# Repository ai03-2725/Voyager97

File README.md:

# Voyager97
A versatile, modern full-functionality keyboard PCB

[PCB Layout](http://www.keyboard-layout-editor.com/#/gists/8a6f76a9ac2c94977268a77ed8a0af57)

#### In light of recent claims that I am 100% liable for any of my open source PCBs, I am adding this disclaimer.
#### I provide these PCBs as a reference for designing keyboard PCBs. Using them within your projects will require a will to do research of one's own and to learn the workings of them, potentially fixing issues if they exist.
# I provide these PCBs without liability and without any guarantees regarding functionality, as expressed in the MIT license under which all of these PCBs are licensed.

### Features
* In-switch LED backlighting
* RGB underglow
* Flex slot cutout for typing comfort
* Decent amount of layout compatibility
* Over-current and static discharge protection
* Fully open-source

### The Voyager PCB Family
The Voyager PCBs offer fully featured PCBs fit for any keyboard, whether mass production or high-end.

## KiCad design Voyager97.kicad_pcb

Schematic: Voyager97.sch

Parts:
C2, C5: 1uF; C_0603
C3, C4: 22pF; C_0603
C6, C7, C8: 0.1uF; C_0603
F1: 500mA; Fuse_SMD1206_Reflow
J1: AVR-ISP-6; Reset_Pretty-Mask
Q1: DSS60601MZ4-13; SOT-223-3_TabPin2
RC1, RC2: 22; R_0603
RC3: 10k; R_0603
RC4: 1k; R_0603
RC5: 1.5k; R_0603
RC6, RC7: 5k1; R_0603
SW1: SW_Push; SKQG-1155865
U1: AT90USB1286-AU; QFN-64-1EP_9x9mm_Pitch0.5mm
U2: PRTR5V0U2X; SOT143B
USB1: HRO-TYPE-C-31-M-12; HRO-TYPE-C-31-M-12-Assembly
Y1: 16MHz; Crystal_SMD_3225-4pin_3.2x2.5mm

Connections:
COL0: U1.61 (PF0); also elsewhere on the board
COL1: U1.60 (PF1); also elsewhere on the board
COL2: U1.59 (PF2); also elsewhere on the board
COL3: U1.58 (PF3); also elsewhere on the board
COL4: U1.57 (PF4); also elsewhere on the board
COL5: U1.56 (PF5); also elsewhere on the board
COL6: U1.55 (PF6); also elsewhere on the board
COL7: U1.54 (PF7); also elsewhere on the board
COL8: U1.51 (PA0); also elsewhere on the board
COL9: U1.50 (PA1); also elsewhere on the board
COL10: U1.49 (PA2); also elsewhere on the board
COL11: U1.48 (PA3); also elsewhere on the board
COL12: U1.47 (PA4); also elsewhere on the board
COL13: U1.46 (PA5); also elsewhere on the board
COL14: U1.45 (PA6); also elsewhere on the board
COL15: U1.36 (PC1); also elsewhere on the board
COL16: U1.35 (PC0); also elsewhere on the board
COL17: U1.34 (PE1); also elsewhere on the board
COL18: U1.33 (PE0); also elsewhere on the board
D+: RC2.2, U1.5 (D+)
D-: RC1.1, U1.4 (D-)
GND: C2.2, C3.2, C4.2, C5.1, C6.1, C7.1, C8.1, J1.6, Q1.3, RC4.2, RC6.1, RC7.1, SW1.1, U1.6 (UGND), U1.22 (GND), U1.53 (GND), U1.63 (GND), U1.65 (GND), U2.1, USB1.1, USB1.12, USB1.13, Y1.2, Y1.4
LEDGND: Q1.2; also elsewhere on the board
MISO: J1.1, U1.13 (PB3)
MOSI: J1.4, U1.12 (PB2)
unnamed: C2.1, U1.7 (UCAP)
unnamed: Q1.1, RC5.2
unnamed: RC1.2, U2.3, USB1.5, USB1.7
unnamed: RC2.1, U2.2, USB1.6, USB1.8
unnamed: RC4.1, U1.43 (PE2/~HWB)
unnamed: RC5.1, U1.17 (PB7)
unnamed: RC6.2, USB1.4
unnamed: RC7.2, USB1.10
RESET: J1.5, RC3.2, SW1.2, U1.20 (~RESET)
ROW0: U1.32 (PD7); also elsewhere on the board
ROW1: U1.38 (PC3); also elsewhere on the board
ROW2: U1.39 (PC4); also elsewhere on the board
ROW3: U1.40 (PC5); also elsewhere on the board
ROW4: U1.41 (PC6); also elsewhere on the board
ROW5: U1.42 (PC7); also elsewhere on the board
SCK: J1.3, U1.11 (PB1)
VCC: F1.2, U2.4, USB1.2, USB1.11
XTAL1: C3.1, U1.24 (XTAL1), Y1.1
XTAL2: C4.1, U1.23 (XTAL2), Y1.3

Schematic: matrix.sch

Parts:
BS1-1: MX-2U
BS1-2, BS2: MX-1U
CL1-1: MX-1.75U
CL1-2: MX-1.25U; MX-1.25U-FLIPPED
D1, D2, D3, D4, D5, D6, D7, D8, D9, D10, D11, D12, D13, D14, D15, D16, D17, D18, D19, D20, D21, D22, D23, D24, D25, D26, D27, D28, D29, D30, D31, D32, D33, D35, D36, D37, D38, D39, D40, D41, D42, D43, D44, D45, D46, D47, D48, D52, D53, D54, D55, D56, D57, D58, D59, D60, D61, D62, D63, D65, D66, D67, D68, D69, D70, D71, D72, D73, D74, D75, D76, D77, D78, D80, D81, D82, D83, D84, D85, D86, D87, D89, D90, D91, D92, D93, D94, D95, D96, D97, D98, D99, D100, D101, D102, D103, D104, D105, D106, D107, D108, D109, D110, D111, D112, D113, D114: SOD-323; D_SOD-123
LM1-1, LM2-1, LM3-1: MX-1.25U
LM1-2: MX-1.5U; MX-1.5U-FLIPPED
LM3-2: MX-1.5U
LS1-1: MX-2.25U
MX_#0_1, MX_#1, MX_#2, MX_#3, MX_#4, MX_#5, MX_#6, MX_#7, MX_#8, MX_#9: MX-1U
MX_'1: MX-1U
MX_,1: MX-1U
MX_-1: MX-1U
MX_.1: MX-1U
MX_/1: MX-1U
MX_;1: MX-1U
MX_=1: MX-1U
MX_A1: MX-1U
MX_B1: MX-1U
MX_C1: MX-1U
MX_D1: MX-1U
MX_DOWN1: MX-1U
MX_E1: MX-1U
MX_ESC1: MX-1U
MX_EX1, MX_EX2, MX_EX3, MX_EX4: MX-1U
MX_F1: MX-1U
MX_FN1, MX_FN2, MX_FN3, MX_FN4, MX_FN5, MX_FN6, MX_FN7, MX_FN8, MX_FN9, MX_FN10, MX_FN11, MX_FN12: MX-1U
MX_G1: MX-1U
MX_H1: MX-1U
MX_I1: MX-1U
MX_J1: MX-1U
MX_K1: MX-1U
MX_L1: MX-1U
MX_LEFT1: MX-1U
MX_M1: MX-1U
MX_N1: MX-1U
MX_NUM1, MX_NUM2, MX_NUM3, MX_NUM4, MX_NUM5, MX_NUM6, MX_NUM7, MX_NUM8, MX_NUM9, MX_NUM10, MX_NUM11, MX_NUM12, MX_NUM13, MX_NUM14, MX_NUM15, MX_NUM16, MX_NUM17, MX_NUM18, MX_NUM19, MX_NUM20, MX_NUM21, MX_NUM22, MX_NUM23, MX_NUM24: MX-1U
MX_NUMEXT2, MX_NUMEXT4, MX_NUMEXT5: MX-2U; MX-2U-ReversedStabilizers
MX_O1: MX-1U
MX_P1: MX-1U
MX_Q1: MX-1U
MX_R1: MX-1U
MX_RESET1: MX-1U
MX_RETURN1: MX-2.25U
MX_RIGHT1: MX-1U
MX_RSHIFT1: MX-1.75U
MX_S1: MX-1U
MX_T1: MX-1U
MX_TAB1: MX-1.5U
MX_U1: MX-1U
MX_UP1: MX-1U
MX_V1: MX-1U
MX_W1: MX-1U
MX_X1: MX-1U
MX_Y1: MX-1U
MX_Z1: MX-1U
MX_[1: MX-1U
MX_\1: MX-1.5U
MX_]1: MX-1U
MX_`1: MX-1U
R1, R2, R3, R4, R5, R6, R7, R8, R9, R10, R11, R12, R13, R14, R15, R16, R17, R18, R19, R20, R21, R22, R23, R24, R25, R26, R27, R28, R29, R30, R31, R32, R33, R34, R35, R36, R37, R38, R39, R40, R41, R42, R43, R44, R45, R46, R47, R48, R49, R50, R52, R53, R54, R55, R56, R57, R58, R59, R60, R61, R62, R63, R65, R66, R67, R68, R69, R70, R71, R72, R73, R74, R75, R76, R77, R78, R80, R81, R82, R83, R84, R85, R86, R87, R89, R90, R91, R95, R96, R97, R98, R99, R100, R101, R102, R103, R104, R105, R106, R107, R108, R109, R110, R111, R112, R113, R114: 1k; R_0603
RM1-1, RM2-1, RM3-1: MX-1U
RM1-2, RM3-2: MX-1.5U; MX-1.5U-FLIPPED
SP1: MX-6.25U; MX-6.25U-ReversedStabilizers
SP2: MX-7U; MX-7U-ReversedStabilizers

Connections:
COL0: CL1-1.1, CL1-2.2, LM1-1.1, LM1-2.1, LS1-1.1, MX_ESC1.1, MX_TAB1.1, MX_`1.1; also elsewhere on the board
COL1: LM2-1.1, LM3-2.2, MX_#1.1, MX_A1.1, MX_Q1.1, MX_Z1.1; also elsewhere on the board
COL2: LM3-1.1, MX_#2.1, MX_FN1.1, MX_S1.1, MX_W1.1, MX_X1.1; also elsewhere on the board
COL3: MX_#3.1, MX_C1.1, MX_D1.1, MX_E1.1, MX_FN2.1; also elsewhere on the board
COL4: MX_#4.1, MX_F1.1, MX_FN3.1, MX_R1.1, MX_V1.1; also elsewhere on the board
COL5: MX_#5.1, MX_B1.1, MX_FN4.1, MX_G1.1, MX_T1.1, SP1.1, SP2.2; also elsewhere on the board
COL6: MX_#6.1, MX_FN5.1, MX_H1.1, MX_N1.1, MX_Y1.1; also elsewhere on the board
COL7: MX_#7.1, MX_FN6.1, MX_J1.1, MX_M1.1, MX_U1.1; also elsewhere on the board
COL8: MX_#8.1, MX_,1.1, MX_FN7.1, MX_I1.1, MX_K1.1; also elsewhere on the board
COL9: MX_#9.1, MX_.1.1, MX_FN8.1, MX_L1.1, MX_O1.1, RM1-1.1, RM1-2.2; also elsewhere on the board
COL10: MX_#0_1.1, MX_/1.1, MX_;1.1, MX_FN9.1, MX_P1.1, RM2-1.1; also elsewhere on the board
COL11: MX_'1.1, MX_-1.1, MX_FN10.1, MX_[1.1, RM3-1.1, RM3-2.2; also elsewhere on the board
COL12: BS2.1, MX_=1.1, MX_FN11.1, MX_LEFT1.1, MX_RSHIFT1.1, MX_]1.1; also elsewhere on the board
COL13: BS1-1.1, BS1-2.1, MX_DOWN1.1, MX_FN12.1, MX_RETURN1.1, MX_UP1.1, MX_\1.1; also elsewhere on the board
COL14: MX_EX1.1, MX_EX2.1, MX_EX3.1, MX_EX4.1, MX_RESET1.1, MX_RIGHT1.1; also elsewhere on the board
COL15: MX_NUM1.1, MX_NUM4.1, MX_NUM8.1, MX_NUM12.1, MX_NUM16.1, MX_NUM20.1, MX_NUMEXT5.1; also elsewhere on the board
COL16: MX_NUM2.1, MX_NUM5.1, MX_NUM9.1, MX_NUM13.1, MX_NUM17.1, MX_NUM21.1; also elsewhere on the board
COL17: MX_NUM3.1, MX_NUM6.1, MX_NUM10.1, MX_NUM14.1, MX_NUM18.1, MX_NUM22.1; also elsewhere on the board
COL18: MX_NUM7.1, MX_NUM11.1, MX_NUM15.1, MX_NUM19.1, MX_NUM23.1, MX_NUM24.1, MX_NUMEXT2.1, MX_NUMEXT4.1; also elsewhere on the board
LEDGND: R1.2, R2.2, R3.2, R4.2, R5.2, R6.2, R7.2, R8.2, R9.2, R10.2, R11.2, R12.2, R13.2, R14.2, R15.2, R16.2, R17.2, R18.2, R19.2, R20.2, R21.2, R22.2, R23.2, R24.2, R25.2, R26.2, R27.2, R28.2, R29.2, R30.2, R31.2, R32.2, R33.2, R34.2, R35.2, R36.2, R37.2, R38.2, R39.2, R40.2, R41.2, R42.2, R43.2, R44.2, R45.2, R46.2, R47.2, R48.2, R49.2, R50.2, R52.2, R53.2, R54.2, R55.2, R56.2, R57.2, R58.2, R59.2, R60.2, R61.2, R62.2, R63.2, R65.2, R66.2, R67.2, R68.2, R69.2, R70.2, R71.2, R72.2, R73.2, R74.2, R75.2, R76.2, R77.2, R78.2, R80.2, R81.2, R82.2, R83.2, R84.2, R85.2, R86.2, R87.2, R89.2, R90.2, R91.2, R95.2, R96.2, R97.2, R98.2, R99.2, R100.2, R101.2, R102.2, R103.2, R104.2, R105.2, R106.2, R107.2, R108.2, R109.2, R110.2, R111.2, R112.2, R113.2, R114.2; also elsewhere on the board
unnamed: BS1-1.2, BS1-2.2, D30.2
unnamed: BS1-1.4, BS1-2.4, R30.1
unnamed: BS2.2, D31.2
unnamed: BS2.4, R31.1
unnamed: CL1-1.2, CL1-2.1, D52.2
unnamed: CL1-1.4, CL1-2.4, R52.1
unnamed: D1.2, MX_ESC1.2
unnamed: D2.2, MX_FN1.2
unnamed: D3.2, MX_FN2.2
unnamed: D4.2, MX_FN3.2
unnamed: D5.2, MX_FN4.2
unnamed: D6.2, MX_FN5.2
unnamed: D7.2, MX_FN6.2
unnamed: D8.2, MX_FN7.2
unnamed: D9.2, MX_FN8.2
unnamed: D10.2, MX_FN9.2
unnamed: D11.2, MX_FN10.2
unnamed: D12.2, MX_FN11.2
unnamed: D13.2, MX_FN12.2
unnamed: D14.2, MX_EX1.2
unnamed: D15.2, MX_RESET1.2
unnamed: D16.2, MX_NUM24.2
unnamed: D17.2, MX_`1.2
unnamed: D18.2, MX_#1.2
unnamed: D19.2, MX_#2.2
unnamed: D20.2, MX_#3.2
unnamed: D21.2, MX_#4.2
unnamed: D22.2, MX_#5.2
unnamed: D23.2, MX_#6.2
unnamed: D24.2, MX_#7.2
unnamed: D25.2, MX_#8.2
unnamed: D26.2, MX_#9.2
unnamed: D27.2, MX_#0_1.2
unnamed: D28.2, MX_-1.2
unnamed: D29.2, MX_=1.2
unnamed: D32.2, MX_EX2.2
unnamed: D33.2, MX_EX3.2
unnamed: D35.2, MX_TAB1.2
unnamed: D36.2, MX_Q1.2
unnamed: D37.2, MX_W1.2
unnamed: D38.2, MX_E1.2
unnamed: D39.2, MX_R1.2
unnamed: D40.2, MX_T1.2
unnamed: D41.2, MX_Y1.2
unnamed: D42.2, MX_U1.2
unnamed: D43.2, MX_I1.2
unnamed: D44.2, MX_O1.2
unnamed: D45.2, MX_P1.2
unnamed: D46.2, MX_[1.2
unnamed: D47.2, MX_]1.2
unnamed: D48.2, MX_\1.2
unnamed: D53.2, MX_A1.2
unnamed: D54.2, MX_S1.2
unnamed: D55.2, MX_D1.2
unnamed: D56.2, MX_F1.2
unnamed: D57.2, MX_G1.2
unnamed: D58.2, MX_H1.2
unnamed: D59.2, MX_J1.2
unnamed: D60.2, MX_K1.2
unnamed: D61.2, MX_L1.2
unnamed: D62.2, MX_;1.2
unnamed: D63.2, MX_'1.2
unnamed: D65.2, MX_RETURN1.2
unnamed: D66.2, MX_UP1.2
unnamed: D67.2, LS1-1.2
unnamed: D68.2, MX_Z1.2
unnamed: D69.2, MX_X1.2
unnamed: D70.2, MX_C1.2
unnamed: D71.2, MX_V1.2
unnamed: D72.2, MX_B1.2
unnamed: D73.2, MX_N1.2
unnamed: D74.2, MX_M1.2
unnamed: D75.2, MX_,1.2
unnamed: D76.2, MX_.1.2
unnamed: D77.2, MX_/1.2
unnamed: D78.2, MX_RSHIFT1.2
unnamed: D80.2, MX_EX4.2
unnamed: D81.2, MX_LEFT1.2
unnamed: D82.2, MX_DOWN1.2
unnamed: D83.2, MX_RIGHT1.2
unnamed: D84.2, LM1-1.2, LM1-2.2
unnamed: D85.2, LM2-1.2, LM3-2.1
unnamed: D86.2, LM3-1.2
unnamed: D87.2, SP1.2, SP2.1
unnamed: D89.2, RM1-1.2, RM1-2.1
unnamed: D90.2, RM2-1.2
unnamed: D91.2, RM3-1.2, RM3-2.1
unnamed: D92.2, MX_NUM1.2
unnamed: D93.2, MX_NUM2.2
unnamed: D94.2, MX_NUM3.2
unnamed: D95.2, MX_NUM4.2
unnamed: D96.2, MX_NUM5.2
unnamed: D97.2, MX_NUM6.2
unnamed: D98.2, MX_NUM7.2
unnamed: D99.2, MX_NUM8.2
unnamed: D100.2, MX_NUM9.2
unnamed: D101.2, MX_NUM10.2
unnamed: D102.2, MX_NUM11.2, MX_NUMEXT2.2
unnamed: D103.2, MX_NUM12.2
unnamed: D104.2, MX_NUM13.2
unnamed: D105.2, MX_NUM14.2
unnamed: D106.2, MX_NUM15.2
unnamed: D107.2, MX_NUM16.2
unnamed: D108.2, MX_NUM17.2
unnamed: D109.2, MX_NUM18.2
unnamed: D110.2, MX_NUM19.2, MX_NUMEXT4.2
unnamed: D111.2, MX_NUM20.2, MX_NUMEXT5.2
unnamed: D112.2, MX_NUM21.2
unnamed: D113.2, MX_NUM22.2
unnamed: D114.2, MX_NUM23.2
unnamed: LM1-1.4, LM1-2.4, R84.1
unnamed: LM2-1.4, LM3-2.4, R85.1
unnamed: LM3-1.4, R86.1
unnamed: LS1-1.4, R67.1
unnamed: MX_#0_1.4, R27.1
unnamed: MX_#1.4, R18.1
unnamed: MX_#2.4, R19.1
unnamed: MX_#3.4, R20.1
unnamed: MX_#4.4, R21.1
unnamed: MX_#5.4, R22.1
unnamed: MX_#6.4, R23.1
unnamed: MX_#7.4, R24.1
unnamed: MX_#8.4, R25.1
unnamed: MX_#9.4, R26.1
unnamed: MX_'1.4, R63.1
unnamed: MX_,1.4, R75.1
unnamed: MX_-1.4, R28.1
unnamed: MX_.1.4, R76.1
unnamed: MX_/1.4, R77.1
unnamed: MX_;1.4, R62.1
unnamed: MX_=1.4, R29.1
unnamed: MX_A1.4, R53.1
unnamed: MX_B1.4, R72.1
unnamed: MX_C1.4, R70.1
unnamed: MX_D1.4, R55.1
unnamed: MX_DOWN1.4, R82.1
unnamed: MX_E1.4, R38.1
unnamed: MX_ESC1.4, R1.1
unnamed: MX_EX1.4, R14.1
unnamed: MX_EX2.4, R49.1
unnamed: MX_EX3.4, R50.1
unnamed: MX_EX4.4, R80.1
unnamed: MX_F1.4, R56.1
unnamed: MX_FN1.4, R2.1
unnamed: MX_FN2.4, R3.1
unnamed: MX_FN3.4, R4.1
unnamed: MX_FN4.4, R5.1
unnamed: MX_FN5.4, R6.1
unnamed: MX_FN6.4, R7.1
unnamed: MX_FN7.4, R8.1
unnamed: MX_FN8.4, R9.1
unnamed: MX_FN9.4, R10.1
unnamed: MX_FN10.4, R11.1
unnamed: MX_FN11.4, R12.1
unnamed: MX_FN12.4, R13.1
unnamed: MX_G1.4, R57.1
unnamed: MX_H1.4, R58.1
unnamed: MX_I1.4, R43.1
unnamed: MX_J1.4, R59.1
unnamed: MX_K1.4, R60.1
unnamed: MX_L1.4, R61.1
unnamed: MX_LEFT1.4, R81.1
unnamed: MX_M1.4, R74.1
unnamed: MX_N1.4, R73.1
unnamed: MX_NUM1.4, R16.1
unnamed: MX_NUM2.4, R32.1
unnamed: MX_NUM3.4, R33.1
unnamed: MX_NUM4.4, R95.1
unnamed: MX_NUM5.4, R96.1
unnamed: MX_NUM6.4, R97.1
unnamed: MX_NUM7.4, R98.1
unnamed: MX_NUM8.4, R99.1
unnamed: MX_NUM9.4, R100.1
unnamed: MX_NUM10.4, R101.1
unnamed: MX_NUM11.4, MX_NUMEXT2.4, R102.1
unnamed: MX_NUM12.4, R103.1
unnamed: MX_NUM13.4, R104.1
unnamed: MX_NUM14.4, R105.1
unnamed: MX_NUM15.4, R106.1
unnamed: MX_NUM16.4, R107.1
unnamed: MX_NUM17.4, R108.1
unnamed: MX_NUM18.4, R109.1
unnamed: MX_NUM19.4, MX_NUMEXT4.4, R110.1
unnamed: MX_NUM20.4, MX_NUMEXT5.4, R111.1
unnamed: MX_NUM21.4, R112.1
unnamed: MX_NUM22.4, R113.1
unnamed: MX_NUM23.4, R114.1
unnamed: MX_NUM24.4, R34.1
unnamed: MX_O1.4, R44.1
unnamed: MX_P1.4, R45.1
unnamed: MX_Q1.4, R36.1
unnamed: MX_R1.4, R39.1
unnamed: MX_RESET1.4, R15.1
unnamed: MX_RETURN1.4, R65.1
unnamed: MX_RIGHT1.4, R83.1
unnamed: MX_RSHIFT1.4, R78.1
unnamed: MX_S1.4, R54.1
unnamed: MX_T1.4, R40.1
unnamed: MX_TAB1.4, R35.1
unnamed: MX_U1.4, R42.1
unnamed: MX_UP1.4, R66.1
unnamed: MX_V1.4, R71.1
unnamed: MX_W1.4, R37.1
unnamed: MX_X1.4, R69.1
unnamed: MX_Y1.4, R41.1
unnamed: MX_Z1.4, R68.1
unnamed: MX_[1.4, R46.1
unnamed: MX_\1.4, R48.1
unnamed: MX_]1.4, R47.1
unnamed: MX_`1.4, R17.1
unnamed: R87.1, SP1.4, SP2.4
unnamed: R89.1, RM1-1.4, RM1-2.4
unnamed: R90.1, RM2-1.4
unnamed: R91.1, RM3-1.4, RM3-2.4
ROW0: D1.1, D2.1, D3.1, D4.1, D5.1, D6.1, D7.1, D8.1, D9.1, D10.1, D11.1, D12.1, D13.1, D15.1, D16.1, D92.1, D93.1, D94.1; also elsewhere on the board
ROW1: D14.1, D17.1, D18.1, D19.1, D20.1, D21.1, D22.1, D23.1, D24.1, D25.1, D26.1, D27.1, D28.1, D29.1, D30.1, D95.1, D96.1, D97.1, D98.1; also elsewhere on the board
ROW2: D32.1, D35.1, D36.1, D37.1, D38.1, D39.1, D40.1, D41.1, D42.1, D43.1, D44.1, D45.1, D46.1, D47.1, D48.1, D99.1, D100.1, D101.1, D102.1; also elsewhere on the board
ROW3: D31.1, D33.1, D52.1, D53.1, D54.1, D55.1, D56.1, D57.1, D58.1, D59.1, D60.1, D61.1, D62.1, D63.1, D65.1, D103.1, D104.1, D105.1, D106.1; also elsewhere on the board
ROW4: D66.1, D67.1, D68.1, D69.1, D70.1, D71.1, D72.1, D73.1, D74.1, D75.1, D76.1, D77.1, D78.1, D80.1, D107.1, D108.1, D109.1, D110.1; also elsewhere on the board
ROW5: D81.1, D82.1, D83.1, D84.1, D85.1, D86.1, D87.1, D89.1, D90.1, D91.1, D111.1, D112.1, D113.1, D114.1; also elsewhere on the board

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
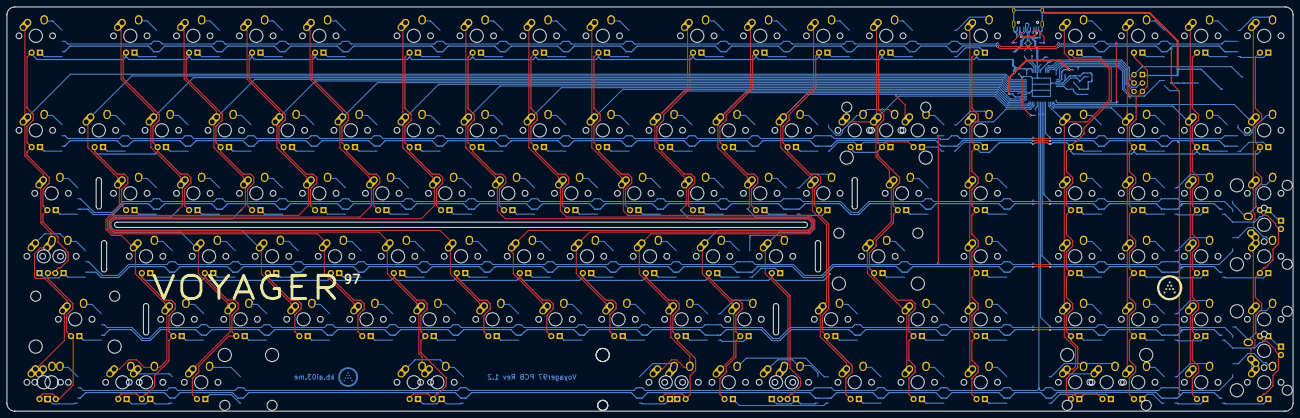
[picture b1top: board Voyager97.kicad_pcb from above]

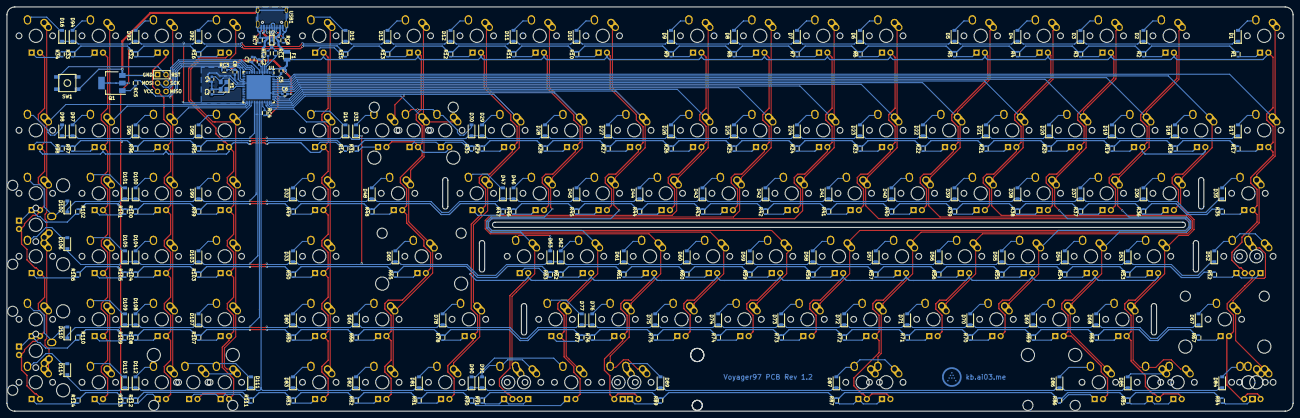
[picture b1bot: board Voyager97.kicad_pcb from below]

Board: 2 copper layers, 388.9 x 122.2 mm, 353 parts (236 on the bottom side), 259 nets.

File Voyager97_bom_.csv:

Component,Description,Part,References,Value,Footprint,Quantity Per PCB,Datasheet,Field8,Field4,Field7,Field6,Field5
1,,MX-1U,"BS1-2 BS2 MX_#0_1 MX_#1 MX_#2 MX_#3 MX_#4 MX_#5 MX_#6 MX_#7 MX_#8 MX_#9 MX_'1 MX_,1 MX_-1 MX_.1 MX_/1 MX_;1 MX_=1 MX_A1 MX_B1 MX_C1 MX_D1 MX_DOWN1 MX_E1 MX_ESC1 MX_EX1 MX_EX2 MX_EX3 MX_EX4 MX_F1 MX_FN1 MX_FN2 MX_FN3 MX_FN4 MX_FN5 MX_FN6 MX_FN7 MX_FN8 MX_FN9 MX_FN10 MX_FN11 MX_FN12 MX_G1 MX_H1 MX_I1 MX_J1 MX_K1 MX_L1 MX_LEFT1 MX_M1 MX_N1 MX_NUM1 MX_NUM2 MX_NUM3 MX_NUM4 MX_NUM5 MX_NUM6 MX_NUM7 MX_NUM8 MX_NUM9 MX_NUM10 MX_NUM11 MX_NUM12 MX_NUM13 MX_NUM14 MX_NUM15 MX_NUM16 MX_NUM17 MX_NUM18 MX_NUM19 MX_NUM20 MX_NUM21 MX_NUM22 MX_NUM23 MX_NUM24 MX_O1 MX_P1 MX_Q1 MX_R1 MX_RESET1 MX_RIGHT1 MX_S1 MX_T1 MX_U1 MX_UP1 MX_V1 MX_W1 MX_X1 MX_Y1 MX_Z1 MX_[1 MX_]1 MX_`1",MX-1U,MX-1U,94,,,,,,
2,,MX-2U,BS1-1,MX-2U,MX-2U,1,,,,,,
3,Unpolarized capacitor,C_Small,C6 C7 C8,0.1uF,C_0603,3,,,,,,
4,Unpolarized capacitor,C_Small,C2 C5,1uF,C_0603,2,,,,,,
5,Unpolarized capacitor,C_Small,C3 C4,22pF,C_0603,2,,,,,,
6,,MX-1.25U,CL1-2,MX-1.25U,MX-1.25U-FLIPPED,1,,,,,,
7,,MX-1.75U,CL1-1,MX-1.75U,MX-1.75U,1,,,,,,
8,"Diode, small symbol",D_Small,D1 D2 D3 D4 D5 D6 D7 D8 D9 D10 D11 D12 D13 D14 D15 D16 D17 D18 D19 D20 D21 D22 D23 D24 D25 D26 D27 D28 D29 D30 D31 D32 D33 D35 D36 D37 D38 D39 D40 D41 D42 D43 D44 D45 D46 D47 D48 D52 D53 D54 D55 D56 D57 D58 D59 D60 D61 D62 D63 D65 D66 D67 D68 D69 D70 D71 D72 D73 D74 D75 D76 D77 D78 D80 D81 D82 D83 D84 D85 D86 D87 D89 D90 D91 D92 D93 D94 D95 D96 D97 D98 D99 D100 D101 D102 D103 D104 D105 D106 D107 D108 D109 D110 D111 D112 D113 D114,SOD-323,D_SOD-123,107,,,,,,
9,"resettable fuse, polymeric positive temperature coefficient (PPTC), small symbol",Polyfuse_Small,F1,500mA,Fuse_SMD1206_Reflow,1,,,,,,
10,Atmel 6-pin ISP connector,AVR-ISP-6,J1,AVR-ISP-6,Reset_Pretty-Mask,1, ~,,,,,
11,,MX-1U,LM1-1,MX-1.25U,MX-1.25U,1,,,,,,
12,,MX-1.25U,LM2-1 LM3-1,MX-1.25U,MX-1.25U,2,,,,,,
13,,MX-1.5U,LM1-2 RM1-2 RM3-2,MX-1.5U,MX-1.5U-FLIPPED,3,,,,,,
14,,MX-1.5U,LM3-2 MX_TAB1 MX_\1,MX-1.5U,MX-1.5U,3,,,,,,
15,,MX-2.25U,LS1-1 MX_RETURN1,MX-2.25U,MX-2.25U,2,,,,,,
16,,MX-1U,MX_RSHIFT1,MX-1.75U,MX-1.75U,1,,,,,,
17,,MX-1U,MX_NUMEXT2 MX_NUMEXT4 MX_NUMEXT5,MX-2U,MX-2U-ReversedStabilizers,3,,,,,,
18,Transistor NPN (general),Q_NPN_BCE,Q1,DSS60601MZ4-13,SOT-223-3_TabPin2,1,,,,,,
19,"Resistor, small symbol",R_Small,R1 R2 R3 R4 R5 R6 R7 R8 R9 R10 R11 R12 R13 R14 R15 R16 R17 R18 R19 R20 R21 R22 R23 R24 R25 R26 R27 R28 R29 R30 R31 R32 R33 R34 R35 R36 R37 R38 R39 R40 R41 R42 R43 R44 R45 R46 R47 R48 R49 R50 R52 R53 R54 R55 R56 R57 R58 R59 R60 R61 R62 R63 R65 R66 R67 R68 R69 R70 R71 R72 R73 R74 R75 R76 R77 R78 R80 R81 R82 R83 R84 R85 R86 R87 R89 R90 R91 R95 R96 R97 R98 R99 R100 R101 R102 R103 R104 R105 R106 R107 R108 R109 R110 R111 R112 R113 R114 RC4,1k,R_0603,108,,,,,,
20,"Resistor, small symbol",R_Small,RC5,1.5k,R_0603,1,,,,,,
21,"Resistor, small symbol",R_Small,RC3,10k,R_0603,1,,,,,,
22,"Resistor, small symbol",R_Small,RC1 RC2,22,R_0603,2,,,,,,
23,"Resistor, small symbol",R_Small,RC6 RC7,5k1,R_0603,2,,,,,,
24,,MX-1.25U,RM1-1 RM2-1 RM3-1,MX-1U,MX-1U,3,,,,,,
25,,MX-6.25U,SP1,MX-6.25U,MX-6.25U-ReversedStabilizers,1,,,,,,
26,,MX-7U,SP2,MX-7U,MX-7U-ReversedStabilizers,1,,,,,,
27,"Push button switch, generic, two pins",SW_Push,SW1,SW_Push,PushButton_6x6mm_TH,1,,,,,,
28,"16MHz, 64kB Flash, 4kB SRAM, 2kB EEPROM, USB 2.0, QFN-64",AT90USB1286-MU,U1,AT90USB1286-AU,QFN-64-1EP_9x9mm_Pitch0.5mm,1,8.69 USD,AT90USB1286-AU,TQFP-64 Microchip,Good,Embedded microcontroller AT90USB1286-AU TQFP 64 _14x14_ Microchip Technology 8-Bit 16 MHz I/O number 48,Microchip
29,,PRTR5V0U2X,U2,PRTR5V0U2X,SOT143B,1,,,,,,
30,,HRO-TYPE-C-31-M-12,USB1,HRO-TYPE-C-31-M-12,HRO-TYPE-C-31-M-12-Assembly,1,,,,,,
31,"Four pin crystal (GND on pins 2 and 4), e.g. in SMD package",Crystal_GND24,Y1,16MHz,Crystal_SMD_3225-4pin_3.2x2.5mm,1,,,,,,
,,,,,,,,,,,,
,,,,,,,,,,,,
,,,,,,,,,,,,
,,,,,,,,,,,,
,,,,,,,,,,,,
Component Groups:,31,,,,,,,,,,,
Component Count:,353,,,,,,,,,,,
Fitted Components:,353,,,,,,,,,,,
Number of PCBs:,1,,,,,,,,,,,
Total components:,353,,,,,,,,,,,
Schematic Version:,,,,,,,,,,,,
Schematic Date:,,,,,,,,,,,,
BoM Date:,11/9/2018 0:58,,,,,,,,,,,
Schematic Source:,Voyager97\Voyager97.sch,,,,,,,,,,,
KiCad Version:,Eeschema (5.0.0),,,,,,,,,,,

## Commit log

2018-11-09 Paste in project files from private files
2018-11-09 Generate production data
2018-11-18 Routing tweaks
2018-11-21 Update KLE
2018-11-24 Add flex cut in center
2018-11-24 Add more flex cutouts
2018-11-25 Adjust cutout location for durability
2018-11-27 Optimizations
    - Crystal placement
    - Tracks near SPI header
2018-11-27 Reposition decoupling capacitor for greater effectiveness
2018-11-29 Locallib doesn't even contain amtra's footprints anymore
2019-01-27 Add render
2019-01-27 Add layout support back
2019-01-27 Update submodules
2019-01-27 Update to new universal logo
